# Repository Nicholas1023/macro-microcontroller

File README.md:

# Macro Microcontroller

A microcontroller and macropad combined in a single PCB, with GPIO pins for external connections.
It can control GPIO pin output using keys or as a normal microcontroller with GPIO pins as input or output. To enable GPIO control, press and hold any key until the LEDs light up. Reset the microcontroller to return to normal mode.

## Schematic

## PCB

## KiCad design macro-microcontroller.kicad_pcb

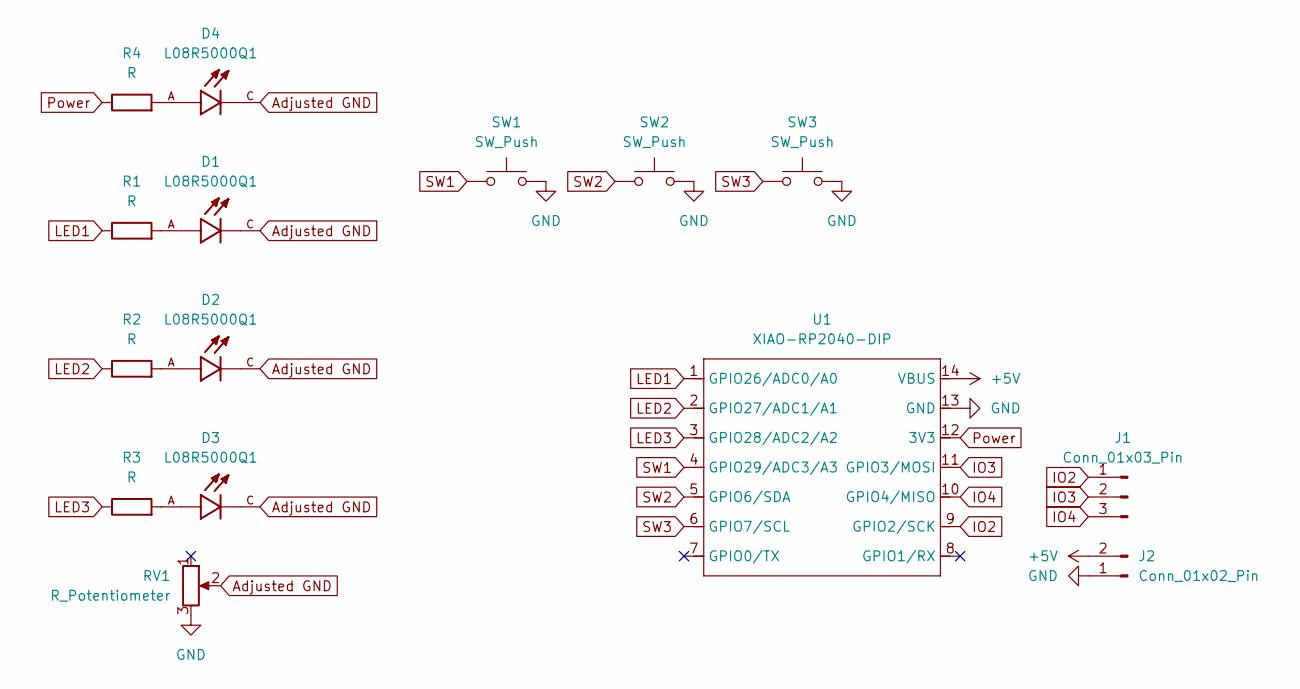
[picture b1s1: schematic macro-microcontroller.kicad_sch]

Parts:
D1, D2, D3, D4: L08R5000Q1; LEDRD254W57D500H1070; PARTREV NA
J1: Conn_01x03_Pin; PinHeader_1x03_P2.54mm_Vertical
J2: Conn_01x02_Pin; PinHeader_1x02_P2.54mm_Vertical
R1, R2, R3, R4: R; R_Axial_DIN0204_L3.6mm_D1.6mm_P5.08mm_Horizontal
RV1: R_Potentiometer; Potentiometer_Vishay_T73YP_Vertical
SW1, SW2, SW3: SW_Push; SW_Cherry_MX_1.00u_PCB
U1: XIAO-RP2040-DIP

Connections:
+5V: J2.2, U1.14 (VBUS)
Adjusted GND: D1.C, D2.C, D3.C, D4.C, RV1.2
GND: J2.1, RV1.3, SW1.2, SW2.2, SW3.2, U1.13 (GND)
IO2: J1.1, U1.9 (GPIO2/SCK)
IO3: J1.2, U1.11 (GPIO3/MOSI)
IO4: J1.3, U1.10 (GPIO4/MISO)
LED1: R1.1, U1.1 (GPIO26/ADC0/A0)
LED2: R2.1, U1.2 (GPIO27/ADC1/A1)
LED3: R3.1, U1.3 (GPIO28/ADC2/A2)
unnamed: D1.A, R1.2
unnamed: D2.A, R2.2
unnamed: D3.A, R3.2
unnamed: D4.A, R4.2
Power: R4.1, U1.12 (3V3)
SW1: SW1.1, U1.4 (GPIO29/ADC3/A3)
SW2: SW2.1, U1.5 (GPIO6/SDA)
SW3: SW3.1, U1.6 (GPIO7/SCL)

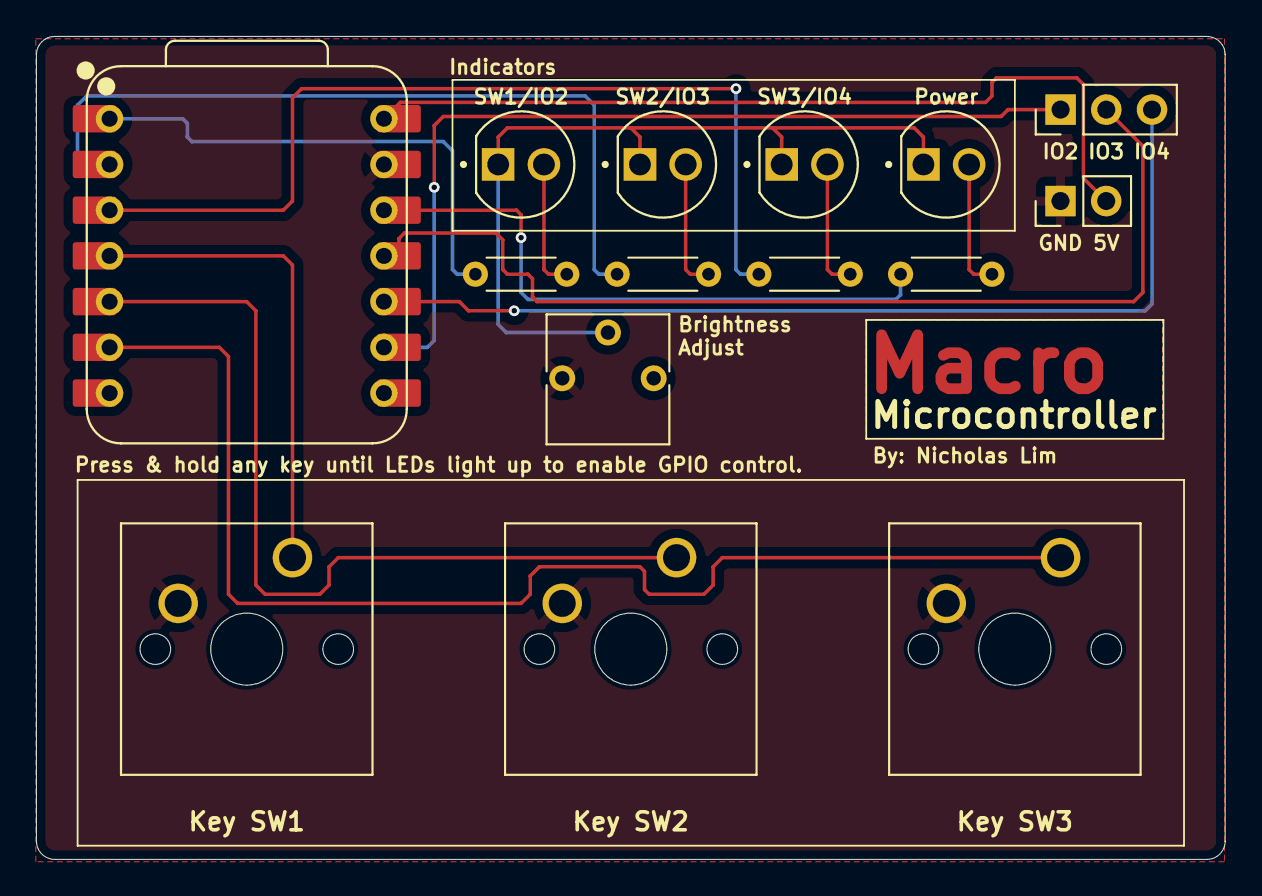
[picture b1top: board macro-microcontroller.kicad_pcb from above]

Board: 2 copper layers, 66.0 x 45.7 mm, 15 parts (0 on the bottom side), 17 nets.

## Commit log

2025-10-31 Edit files
2025-10-31 Rewire power LED to 3V
2025-10-31 Update schematic
2025-10-31 Update PCB files
2025-11-01 Add brightness adjust and edit firmware
2025-11-01 Update firmware
2025-11-01 Edit placement of pins
2025-11-02 Update files
2025-11-02 update filename
2025-11-05 Fix sample program error
2025-11-07 Edit PCB silkscreen
2025-11-07 Edit silkscreen text
2025-11-07 Rename switches as SW
2025-11-07 Update GPIO pin labels
2025-11-08 Move GPIO pin placement
2025-11-08 Add ground plane
2025-11-08 Edit ground plane
2025-11-11 Reroute GPIO pins
2025-12-10 Minor edits to firmware and schematic
